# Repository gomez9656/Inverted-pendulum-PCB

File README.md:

# Inverted-pendulum-PCB
PCB for an inverted pendulum, one layer.

In my college, I had the opportunity to participate in the design of a PCB for an inverted pendulum that used PID control. 

The pendulum used an Arduino Mega that controlled the motors, and my job was to design a PCB shield for the Arduino Mega, so it can be able to fulfill other hardware requirements. I also did a lot of reverse engineering because there were no schematics of the circuit that was working on the pendulum. so it was a very good experience.

I prototyped the PCB shield using an SRM-20 GNC machine, as you can see in the images, the PCB has a lot of components and traces, and I had the requirements to do this in only one layer, so in this way, I can build the prototype very fast using the SRM-20.

In the file section, you can see an image of the board. It is very poor welded(it was my first big project). I was able to prototype it very fast using the Excellon_Gcode, which you can check on my Excellen_Gcode repository.

Don't hesitate to ask me anything if you are looking to do something similar.

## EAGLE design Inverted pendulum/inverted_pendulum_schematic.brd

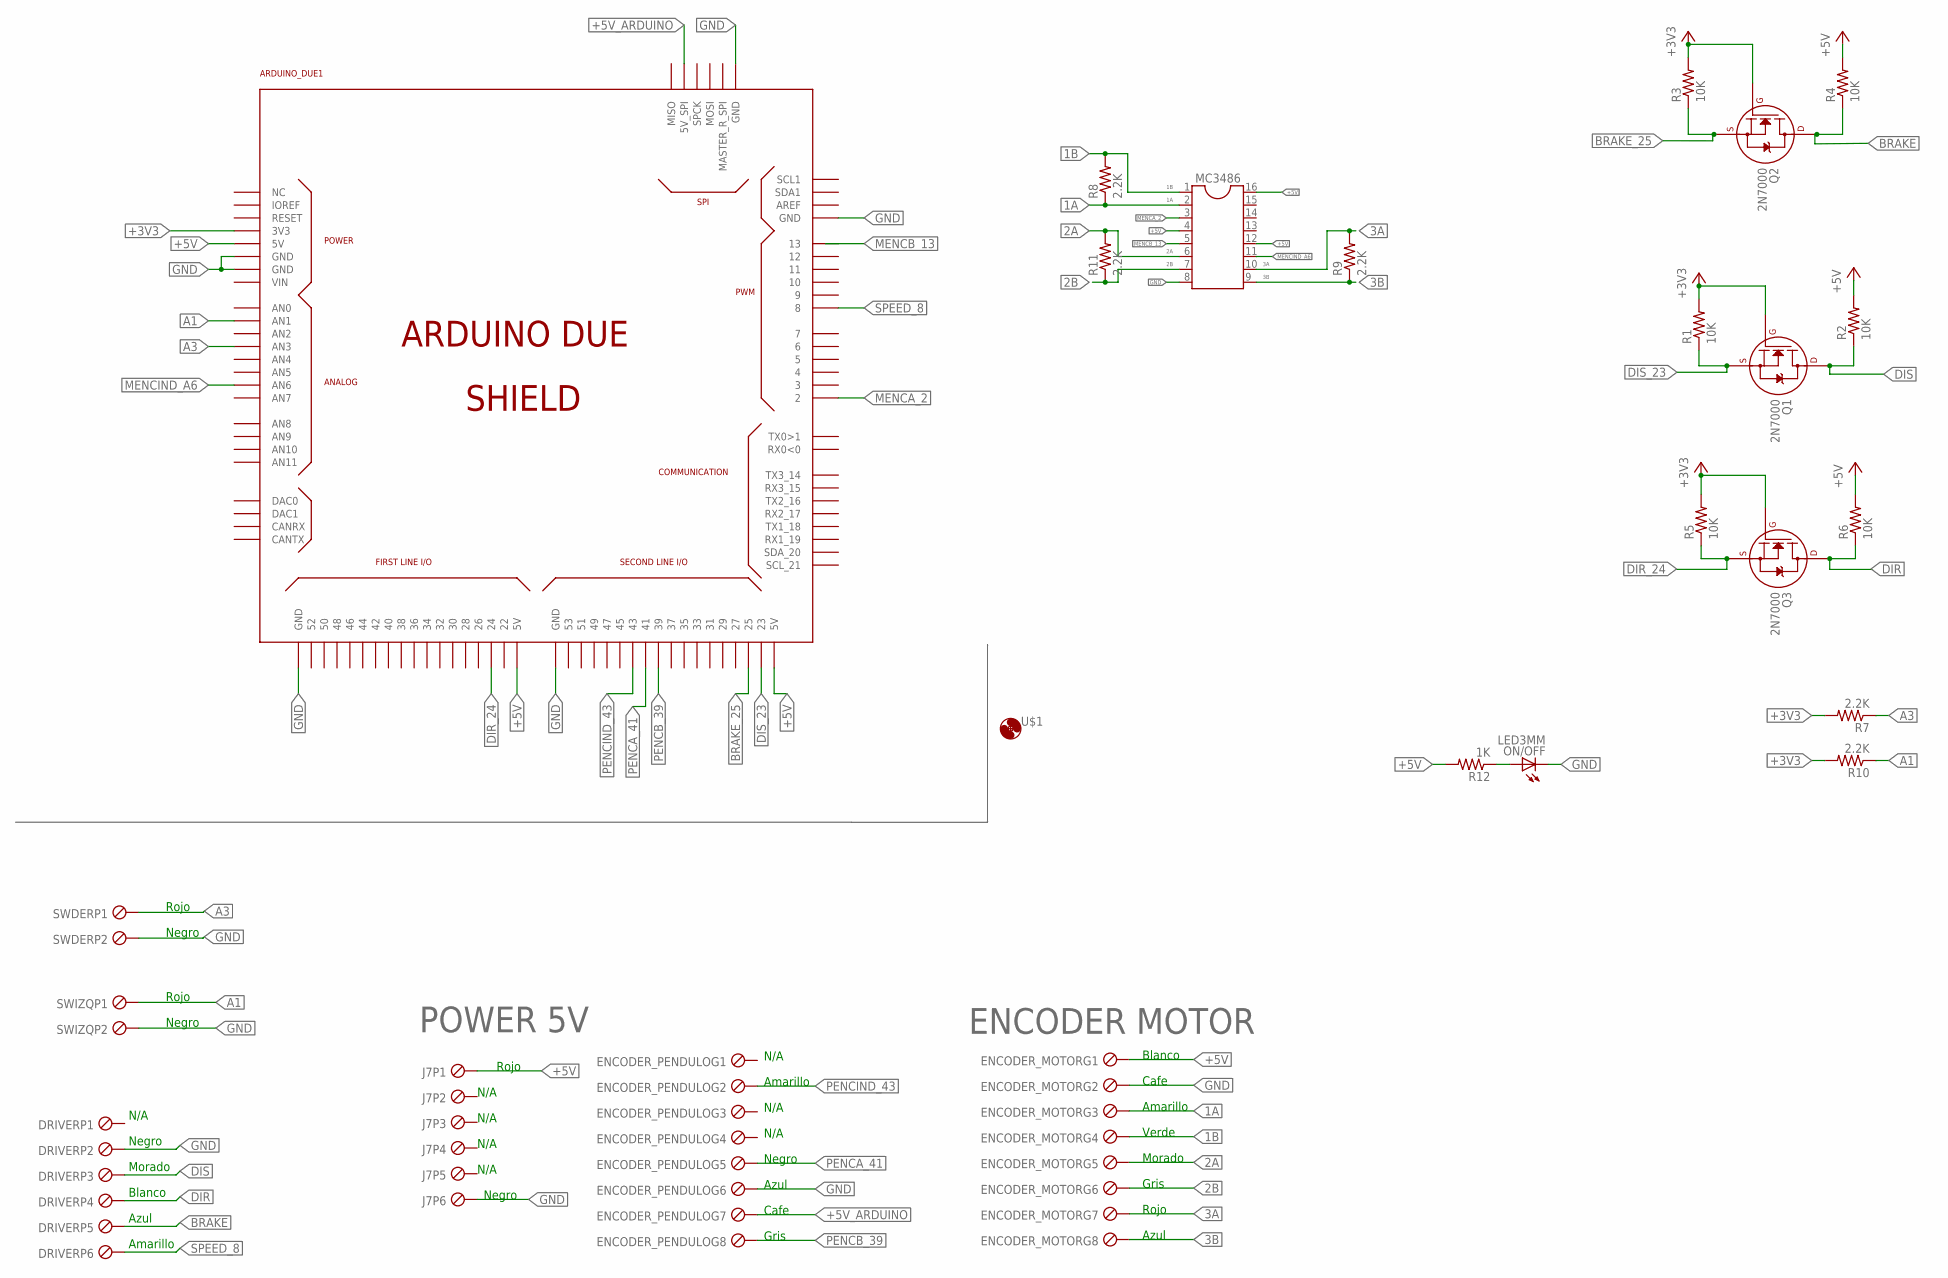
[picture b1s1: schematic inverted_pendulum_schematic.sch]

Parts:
ARDUINO_DUE1: ARDUINO_DUE_SHIELD
DRIVER: PTSM1/6-2,50_TH; 6PTSMTH
ENCODER_MOTOR: PTSM1/8-2,50_TH; 8PTSMTH
ENCODER_PENDULO: PTSM1/8-2,50_TH; 8PTSMTH
J7: PTSM1/6-2,50_TH; 6PTSMTH
MC3486: DIL16S; SOCKET-16
ON/OFF: LED3MM
Q1, Q2, Q3: 2N7000; TO-92
R1, R2, R3, R4, R5, R6: 10K; 0207/10
R7, R8, R9, R10, R11: 2.2K; 0207/10
R12: 1K; 0207/10
SWDER: PTSM1/2-2,50_TH; 2PTSMTH
SWIZQ: PTSM1/2-2,50_TH; 2PTSMTH
U$1: FIDUCIAL; ROLAND_1

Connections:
1A: ENCODER_MOTOR.P$3, MC3486.2, R8.1
1B: ENCODER_MOTOR.P$4, MC3486.1, R8.2
2A: ENCODER_MOTOR.P$5, MC3486.6, R11.2
2B: ENCODER_MOTOR.P$6, MC3486.7, R11.1
3A: ENCODER_MOTOR.P$7, MC3486.10, R9.2
3B: ENCODER_MOTOR.P$8, MC3486.9, R9.1
+3V3: ARDUINO_DUE1.3V3, Q1.2 (G), Q2.2 (G), Q3.2 (G), R1.2, R3.2, R5.2, R7.2, R10.2
+5V: ARDUINO_DUE1.5V0 (5V), ARDUINO_DUE1.5V0_1 (5V), ARDUINO_DUE1.5V0_2 (5V), ENCODER_MOTOR.P$1, J7.P$1, MC3486.4, MC3486.12, MC3486.16, R2.2, R4.2, R6.2, R12.2
+5V_ARDUINO: ARDUINO_DUE1.5V_2 (5V_SPI), ENCODER_PENDULO.P$7
A1: ARDUINO_DUE1.A1 (AN1), R10.1, SWIZQ.1
A3: ARDUINO_DUE1.A3 (AN3), R7.1, SWDER.1
BRAKE: DRIVER.P$5, Q2.3 (D), R4.1
BRAKE_25: ARDUINO_DUE1.25, Q2.1 (S), R3.1
DIR: DRIVER.P$4, Q3.3 (D), R6.1
DIR_24: ARDUINO_DUE1.24, Q3.1 (S), R5.1
DIS: DRIVER.P$3, Q1.3 (D), R2.1
DIS_23: ARDUINO_DUE1.23, Q1.1 (S), R1.1
GND: ARDUINO_DUE1.GND, ARDUINO_DUE1.GND_1 (GND), ARDUINO_DUE1.GND_2 (GND), ARDUINO_DUE1.GND_3 (GND), ARDUINO_DUE1.GND_4 (GND), ARDUINO_DUE1.GND_5 (GND), DRIVER.P$2, ENCODER_MOTOR.P$2, ENCODER_PENDULO.P$6, J7.P$6, MC3486.8, ON/OFF.K (C), SWDER.2, SWIZQ.2
MENCA_2: ARDUINO_DUE1.2, MC3486.3
MENCB_13: ARDUINO_DUE1.13, MC3486.5
MENCIND_A6: ARDUINO_DUE1.A6 (AN6), MC3486.11
unnamed: ON/OFF.A, R12.1
PENCA_41: ARDUINO_DUE1.41, ENCODER_PENDULO.P$5
PENCB_39: ARDUINO_DUE1.39, ENCODER_PENDULO.P$8
PENCIND_43: ARDUINO_DUE1.43, ENCODER_PENDULO.P$2
SPEED_8: ARDUINO_DUE1.8, DRIVER.P$6

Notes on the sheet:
Azul
Rojo
Gris
Morado
Verde
Amarillo
Cafe
Blanco
N/A
Negro
ENCODER MOTOR
POWER 5V

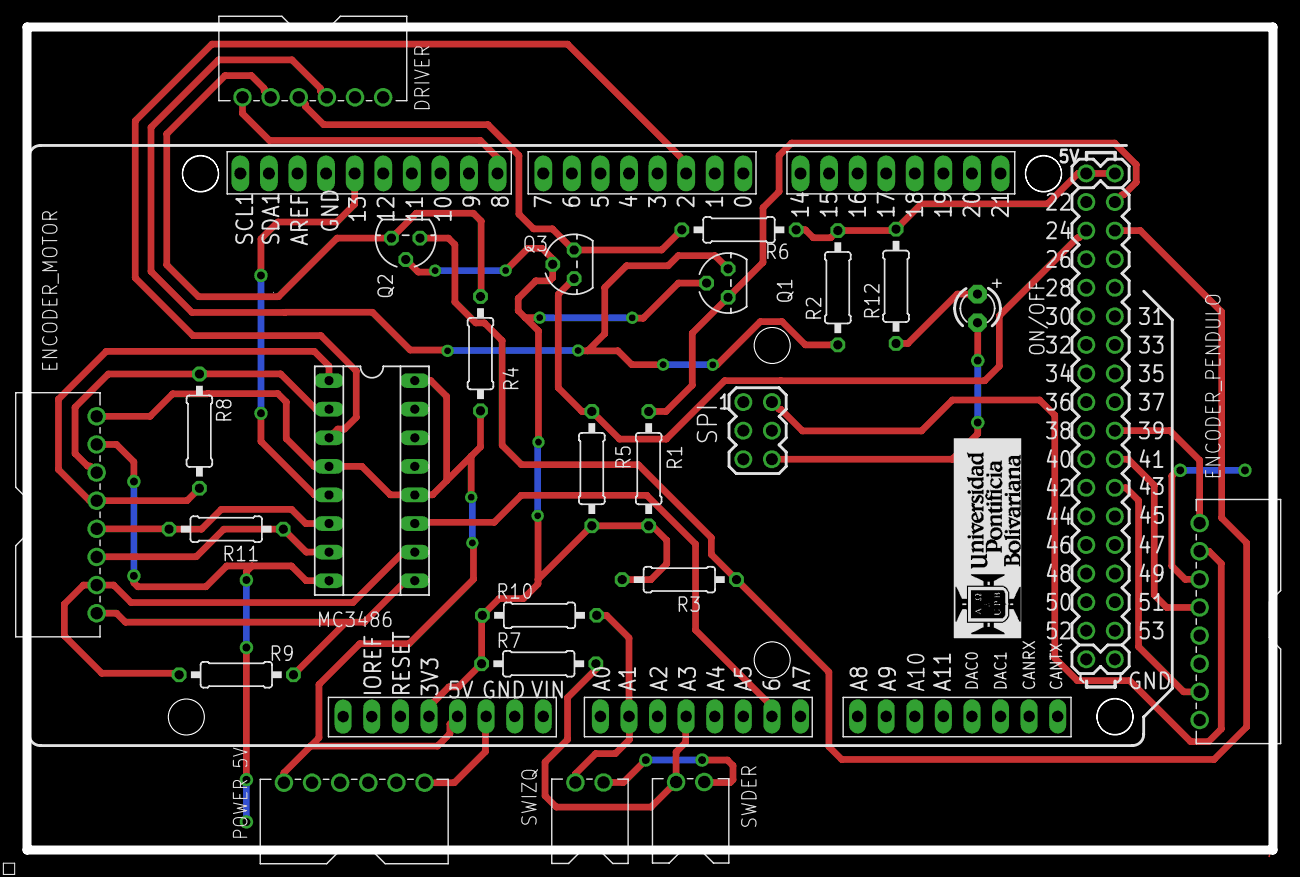
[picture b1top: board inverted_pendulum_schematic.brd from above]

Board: 2 copper layers, 110.7 x 73.2 mm, 25 parts (0 on the bottom side), 26 nets.
